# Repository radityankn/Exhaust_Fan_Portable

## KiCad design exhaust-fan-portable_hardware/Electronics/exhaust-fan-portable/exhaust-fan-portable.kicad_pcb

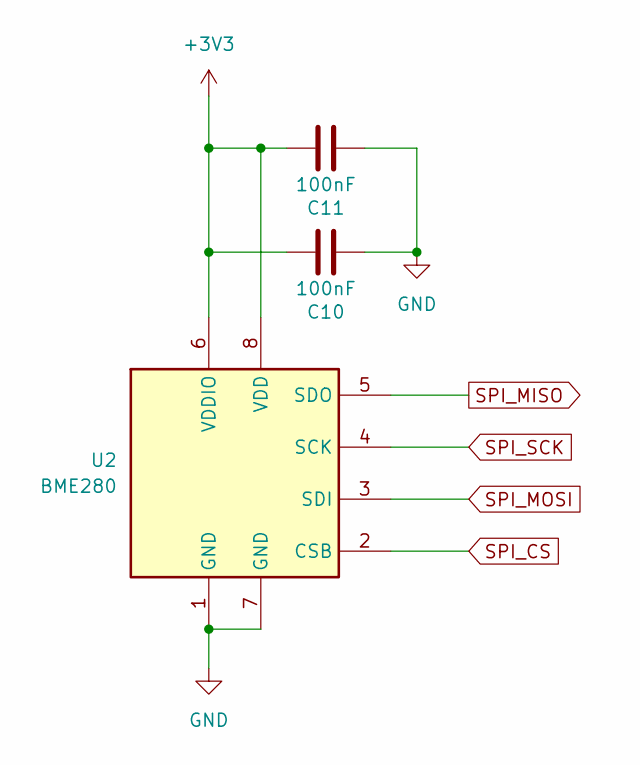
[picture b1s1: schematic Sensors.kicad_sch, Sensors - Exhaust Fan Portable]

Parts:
C10, C11: 100nF; C_0603_1608Metric_Pad1.08x0.95mm_HandSolder
U2: BME280; Bosch_LGA-8_2.5x2.5mm_P0.65mm_ClockwisePinNumbering

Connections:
+3V3: C10.2, C11.2, U2.6 (VDDIO), U2.8 (VDD); also elsewhere on the board
GND: C10.1, C11.1, U2.1 (GND), U2.7 (GND); also elsewhere on the board
SPI_CS: U2.2 (CSB); also elsewhere on the board
SPI_MISO: U2.5 (SDO); also elsewhere on the board
SPI_MOSI: U2.3 (SDI); also elsewhere on the board
SPI_SCK: U2.4 (SCK); also elsewhere on the board

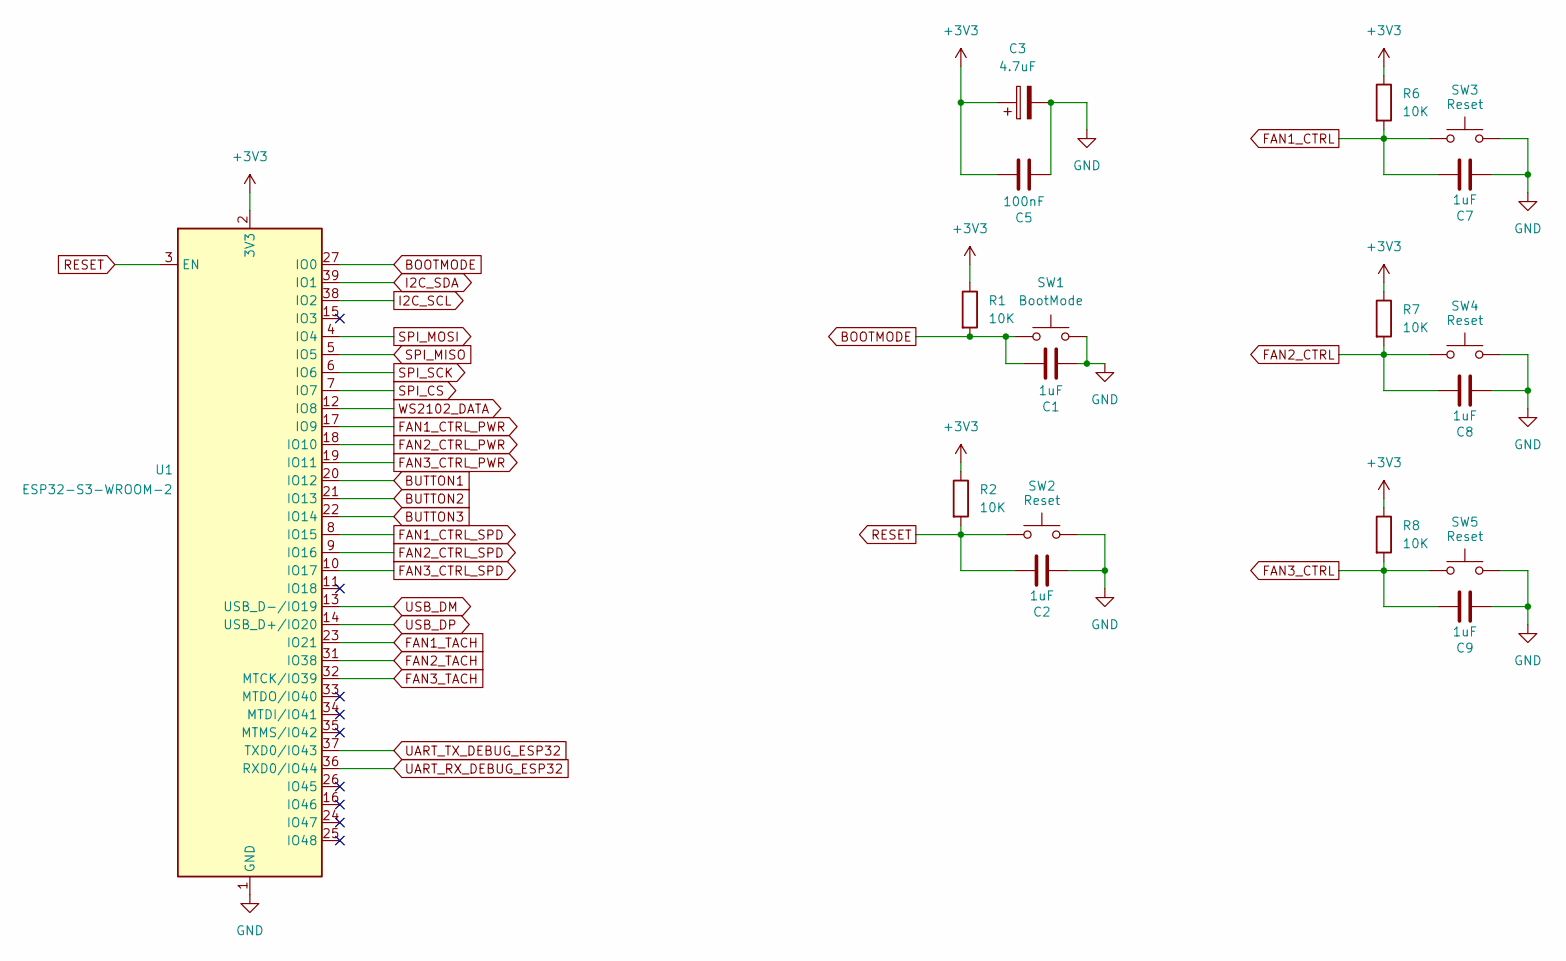
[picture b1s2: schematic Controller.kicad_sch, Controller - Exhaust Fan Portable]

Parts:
C1, C2, C7, C8, C9: 1uF; C_0805_2012Metric_Pad1.18x1.45mm_HandSolder
C3: 4.7uF; C_1206_3216Metric_Pad1.33x1.80mm_HandSolder
C5: 100nF; C_0603_1608Metric_Pad1.08x0.95mm_HandSolder
R1, R2, R6, R7, R8: 10K; R_0603_1608Metric_Pad0.98x0.95mm_HandSolder
SW1: BootMode; SW_Push_SPST_NO_Alps_SKRK
SW2, SW3, SW4, SW5: Reset; SW_Push_SPST_NO_Alps_SKRK
U1: ESP32-S3-WROOM-2

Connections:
+3V3: C3.1, C5.1, R1.1, R2.1, R6.1, R7.1, R8.1, U1.2 (3V3); also elsewhere on the board
BOOTMODE: C1.1, R1.2, SW1.1, U1.27 (IO0)
BUTTON1: U1.20 (IO12)
BUTTON2: U1.21 (IO13)
BUTTON3: U1.22 (IO14)
FAN1_CTRL: C7.2, R6.2, SW3.2
FAN1_CTRL_PWR: U1.17 (IO9); also elsewhere on the board
FAN1_CTRL_SPD: U1.8 (IO15); also elsewhere on the board
FAN1_TACH: U1.23 (IO21); also elsewhere on the board
FAN2_CTRL: C8.2, R7.2, SW4.2
FAN2_CTRL_PWR: U1.18 (IO10); also elsewhere on the board
FAN2_CTRL_SPD: U1.9 (IO16); also elsewhere on the board
FAN2_TACH: U1.31 (IO38); also elsewhere on the board
FAN3_CTRL: C9.2, R8.2, SW5.2
FAN3_CTRL_PWR: U1.19 (IO11); also elsewhere on the board
FAN3_CTRL_SPD: U1.10 (IO17); also elsewhere on the board
FAN3_TACH: U1.32 (MTCK/IO39); also elsewhere on the board
GND: C1.2, C2.1, C3.2, C5.2, C7.1, C8.1, C9.1, SW1.2, SW2.1, SW3.1, SW4.1, SW5.1, U1.1 (GND), U1.40 (GND), U1.41 (GND); also elsewhere on the board
I2C_SCL: U1.38 (IO2); also elsewhere on the board
I2C_SDA: U1.39 (IO1); also elsewhere on the board
RESET: C2.2, R2.2, SW2.2, U1.3 (EN)
SPI_CS: U1.7 (IO7); also elsewhere on the board
SPI_MISO: U1.5 (IO5); also elsewhere on the board
SPI_MOSI: U1.4 (IO4); also elsewhere on the board
SPI_SCK: U1.6 (IO6); also elsewhere on the board
UART_RX_DEBUG_ESP32: U1.36 (RXD0/IO44); also elsewhere on the board
UART_TX_DEBUG_ESP32: U1.37 (TXD0/IO43); also elsewhere on the board
USB_DM: U1.13 (USB_D-/IO19); also elsewhere on the board
USB_DP: U1.14 (USB_D+/IO20); also elsewhere on the board
WS2102_DATA: U1.12 (IO8); also elsewhere on the board

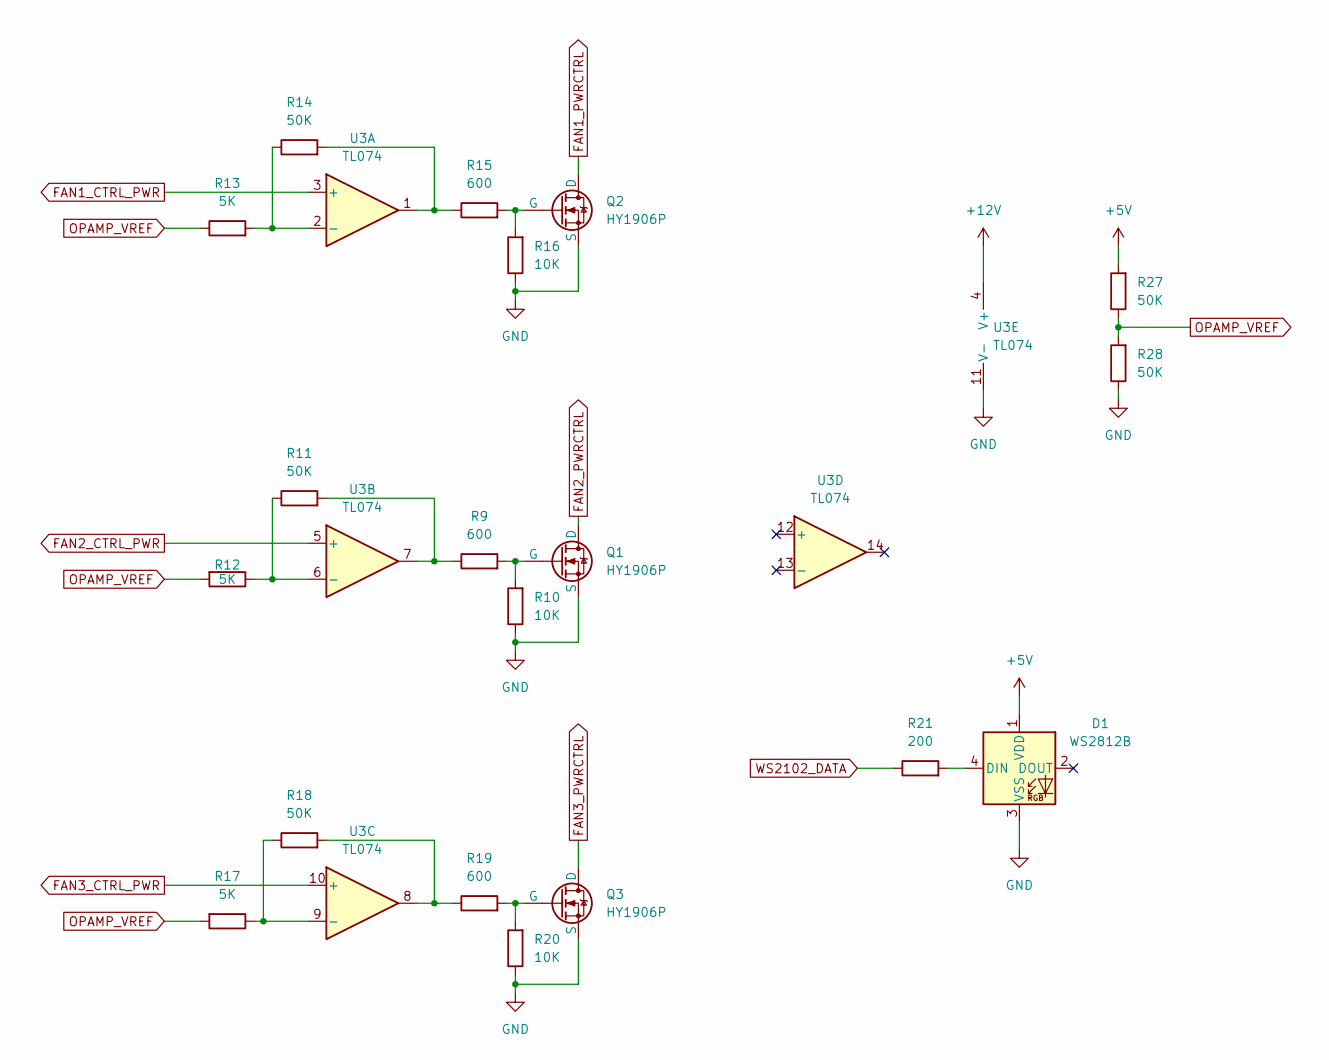
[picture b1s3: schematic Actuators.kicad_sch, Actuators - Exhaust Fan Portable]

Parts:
D1: WS2812B; LED_WS2812B_PLCC4_5.0x5.0mm_P3.2mm
Q1, Q2, Q3: HY1906P; TO-263-2
R9, R15, R19: 600; R_1206_3216Metric_Pad1.30x1.75mm_HandSolder
R10, R16, R20: 10K; R_0603_1608Metric_Pad0.98x0.95mm_HandSolder
R11, R14, R18, R27, R28: 50K; R_0603_1608Metric_Pad0.98x0.95mm_HandSolder
R12, R13, R17: 5K; R_0603_1608Metric_Pad0.98x0.95mm_HandSolder
R21: 200; R_1206_3216Metric_Pad1.30x1.75mm_HandSolder
U3: TL074; SOIC-14_3.9x8.7mm_P1.27mm

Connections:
+5V: D1.1 (VDD), R27.2; also elsewhere on the board
+12V: U3.4 (V+)
FAN1_CTRL_PWR: U3.3 (+); also elsewhere on the board
FAN1_PWRCTRL: Q2.1 (D); also elsewhere on the board
FAN2_CTRL_PWR: U3.5 (+); also elsewhere on the board
FAN2_PWRCTRL: Q1.1 (D); also elsewhere on the board
FAN3_CTRL_PWR: U3.10 (+); also elsewhere on the board
FAN3_PWRCTRL: Q3.1 (D); also elsewhere on the board
GND: D1.3 (VSS), Q1.3 (S), Q2.3 (S), Q3.3 (S), R10.1, R16.1, R20.1, R28.1, U3.11 (V-); also elsewhere on the board
unnamed: D1.4 (DIN), R21.2
unnamed: Q1.2 (G), R9.2, R10.2
unnamed: Q2.2 (G), R15.2, R16.2
unnamed: Q3.2 (G), R19.2, R20.2
unnamed: R9.1, R11.2, U3.7
unnamed: R14.2, R15.1, U3.1
unnamed: R18.2, R19.1, U3.8
unnamed: R13.2, R14.1, U3.2 (-)
unnamed: R11.1, R12.1, U3.6 (-)
unnamed: R17.1, R18.1, U3.9 (-)
OPAMP_VREF: R12.2, R13.1, R17.2, R27.1, R28.2
WS2102_DATA: R21.1; also elsewhere on the board

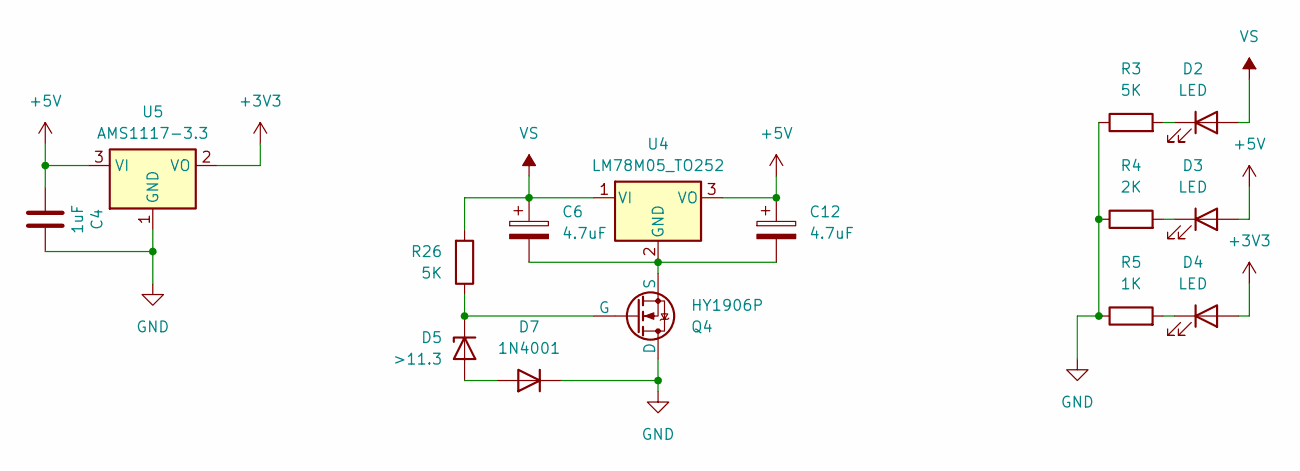
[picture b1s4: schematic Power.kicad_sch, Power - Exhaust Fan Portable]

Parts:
C4: 1uF; C_0805_2012Metric_Pad1.18x1.45mm_HandSolder
C6, C12: 4.7uF; C_1206_3216Metric_Pad1.33x1.80mm_HandSolder
D2, D3, D4: LED; LED_0603_1608Metric_Pad1.05x0.95mm_HandSolder
D5: >11.3; D_1206_3216Metric_Pad1.42x1.75mm_HandSolder
D7: 1N4001; D_SOD-323_HandSoldering
Q4: HY1906P; TO-263-2
R3, R26: 5K; R_0603_1608Metric_Pad0.98x0.95mm_HandSolder
R4: 2K; R_0603_1608Metric_Pad0.98x0.95mm_HandSolder
R5: 1K; R_0603_1608Metric_Pad0.98x0.95mm_HandSolder
U4: LM78M05_TO252; TO-252-2
U5: AMS1117-3.3; SOT-223-3_TabPin2

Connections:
+3V3: D4.2 (A), U5.2 (VO); also elsewhere on the board
+5V: C4.2, C12.1, D3.2 (A), U4.3 (VO), U5.3 (VI); also elsewhere on the board
GND: C4.1, D7.1 (K), Q4.1 (D), R3.1, R4.1, R5.1, U5.1 (GND); also elsewhere on the board
unnamed: D2.1 (K), R3.2
unnamed: D3.1 (K), R4.2
unnamed: D4.1 (K), R5.2
unnamed: D5.2 (A), D7.2 (A)
unnamed: D5.1 (K), Q4.2 (G), R26.1
unnamed: C6.2, C12.2, Q4.3 (S), U4.2 (GND)
VS: C6.1, D2.2 (A), R26.2, U4.1 (VI); also elsewhere on the board

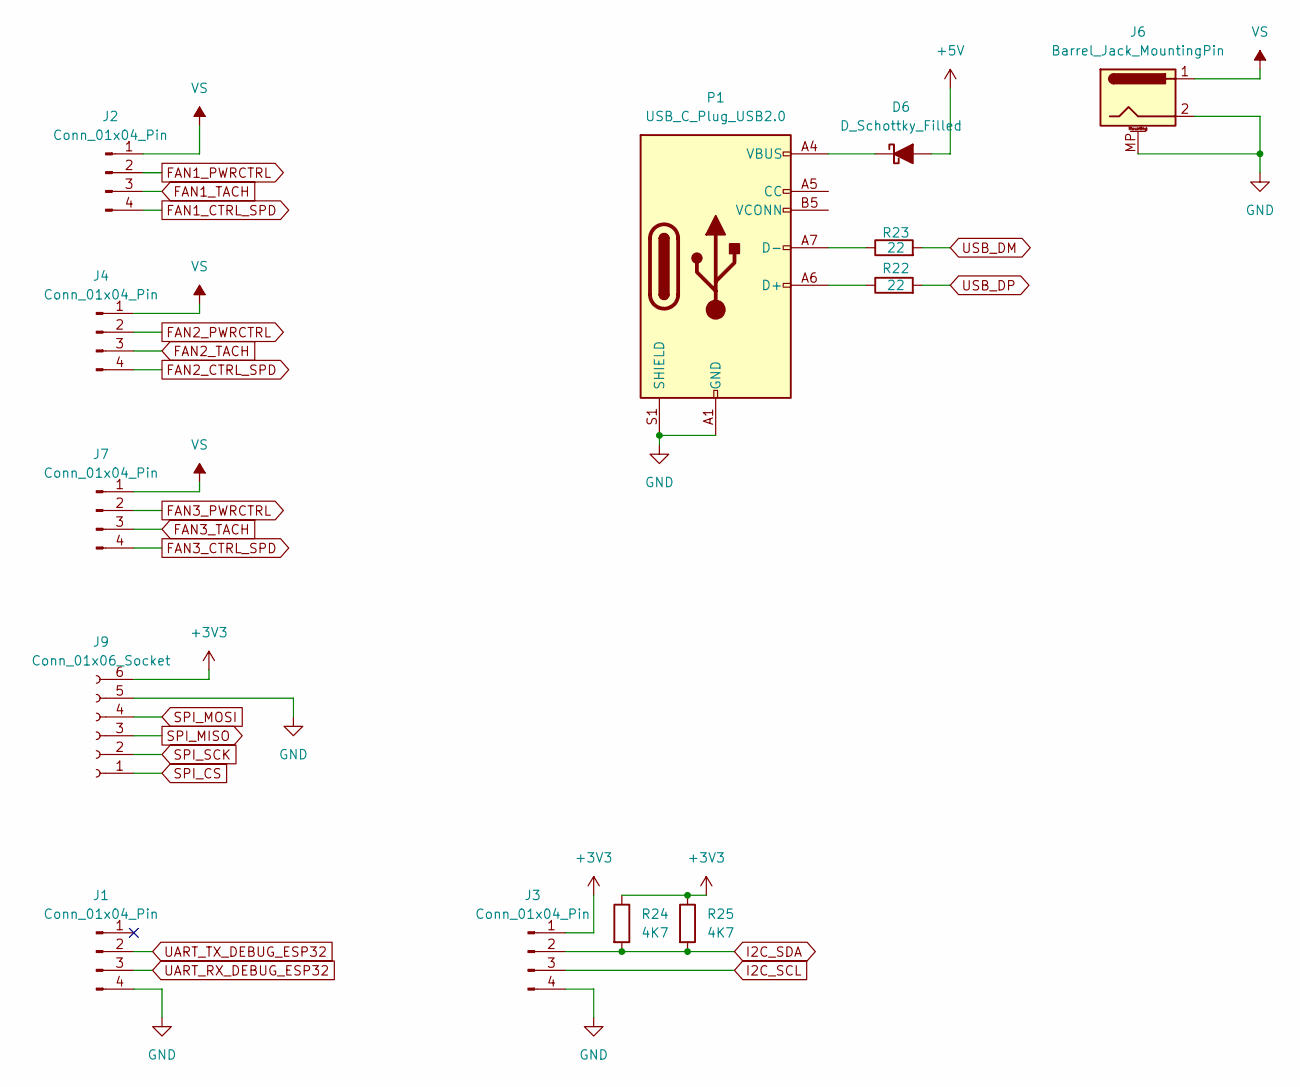
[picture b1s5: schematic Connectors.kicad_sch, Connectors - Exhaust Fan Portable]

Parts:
D6: D_Schottky_Filled; D_0603_1608Metric_Pad1.05x0.95mm_HandSolder
J1, J2, J3, J4, J7: Conn_01x04_Pin; PinHeader_1x04_P2.54mm_Vertical
J6: Barrel_Jack_MountingPin; BarrelJack_Horizontal
J9: Conn_01x06_Socket; PinSocket_1x06_P2.54mm_Vertical
P1: USB_C_Plug_USB2.0; USB_C_Receptacle_G-Switch_GT-USB-7010ASV
R22, R23: 22; R_0603_1608Metric_Pad0.98x0.95mm_HandSolder
R24, R25: 4K7; R_0603_1608Metric_Pad0.98x0.95mm_HandSolder

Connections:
+3V3: J3.1, J9.6, R24.1, R25.1; also elsewhere on the board
+5V: D6.2 (A); also elsewhere on the board
FAN1_CTRL_SPD: J2.4; also elsewhere on the board
FAN1_PWRCTRL: J2.2; also elsewhere on the board
FAN1_TACH: J2.3; also elsewhere on the board
FAN2_CTRL_SPD: J4.4; also elsewhere on the board
FAN2_PWRCTRL: J4.2; also elsewhere on the board
FAN2_TACH: J4.3; also elsewhere on the board
FAN3_CTRL_SPD: J7.4; also elsewhere on the board
FAN3_PWRCTRL: J7.2; also elsewhere on the board
FAN3_TACH: J7.3; also elsewhere on the board
GND: J1.4, J3.4, J6.2, J6.MP (MountPin), J9.5, P1.A1 (GND), P1.A12 (GND), P1.B1 (GND), P1.B12 (GND), P1.S1 (SHIELD); also elsewhere on the board
I2C_SCL: J3.3; also elsewhere on the board
I2C_SDA: J3.2, R24.2, R25.2; also elsewhere on the board
unnamed: D6.1 (K), P1.A4 (VBUS), P1.A9 (VBUS), P1.B4 (VBUS), P1.B9 (VBUS)
unnamed: P1.A6 (D+), R22.1
unnamed: P1.A7 (D-), R23.1
SPI_CS: J9.1; also elsewhere on the board
SPI_MISO: J9.3; also elsewhere on the board
SPI_MOSI: J9.4; also elsewhere on the board
SPI_SCK: J9.2; also elsewhere on the board
UART_RX_DEBUG_ESP32: J1.3; also elsewhere on the board
UART_TX_DEBUG_ESP32: J1.2; also elsewhere on the board
USB_DM: R23.2; also elsewhere on the board
USB_DP: R22.2; also elsewhere on the board
VS: J2.1, J4.1, J6.1, J7.1; also elsewhere on the board

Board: 2 copper layers, 69 parts (0 on the bottom side), 52 nets, no tracks yet.

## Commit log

2025-12-27 Initial commit for exhaust fan repo
2025-12-27 add README in front
2025-12-27 1st trial POC FAN
2025-12-28 Added hardware data
2025-12-28 Added driver source codes
2025-12-30 layed out rough schematic and added sensor comparison
2026-01-03 Create new directory
2026-01-03 Added necessary documentation
    Added various datasheets required for design process
2026-01-03 added 3D mechanical assembly (raw sketch)
2026-01-03 Changed directory structures
2026-01-07 fixed case design
2026-01-11 added mechanical casing v1 along with electronic boards
2026-01-25 updated mechanical information
2026-02-02 completed the mechanical assembly (90%)
